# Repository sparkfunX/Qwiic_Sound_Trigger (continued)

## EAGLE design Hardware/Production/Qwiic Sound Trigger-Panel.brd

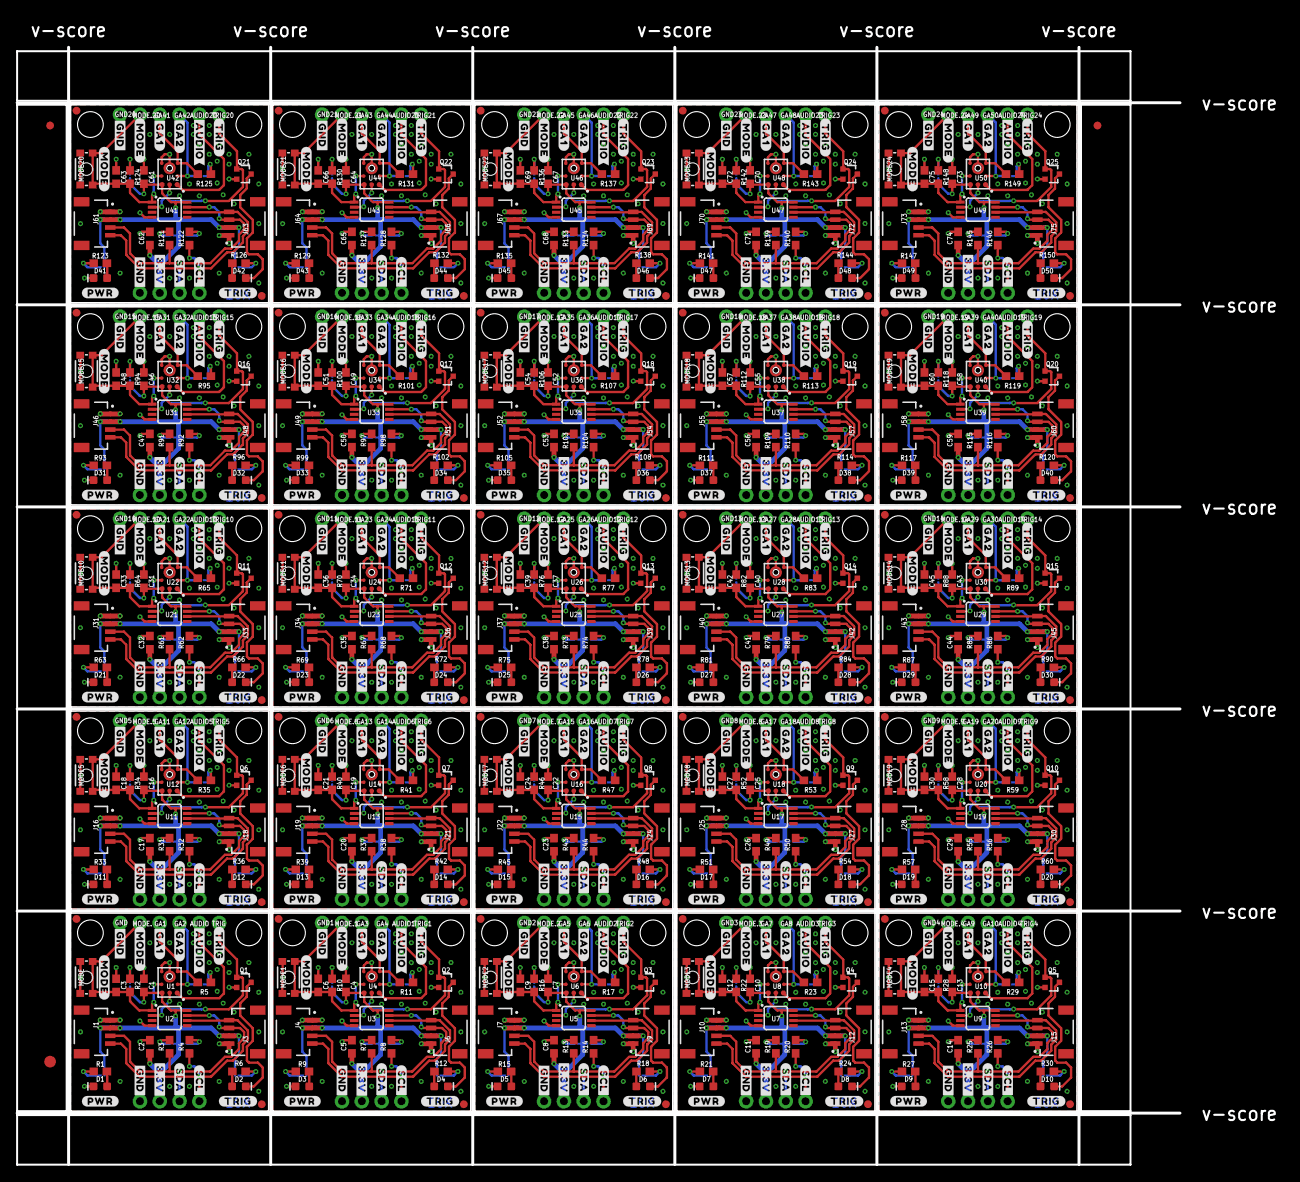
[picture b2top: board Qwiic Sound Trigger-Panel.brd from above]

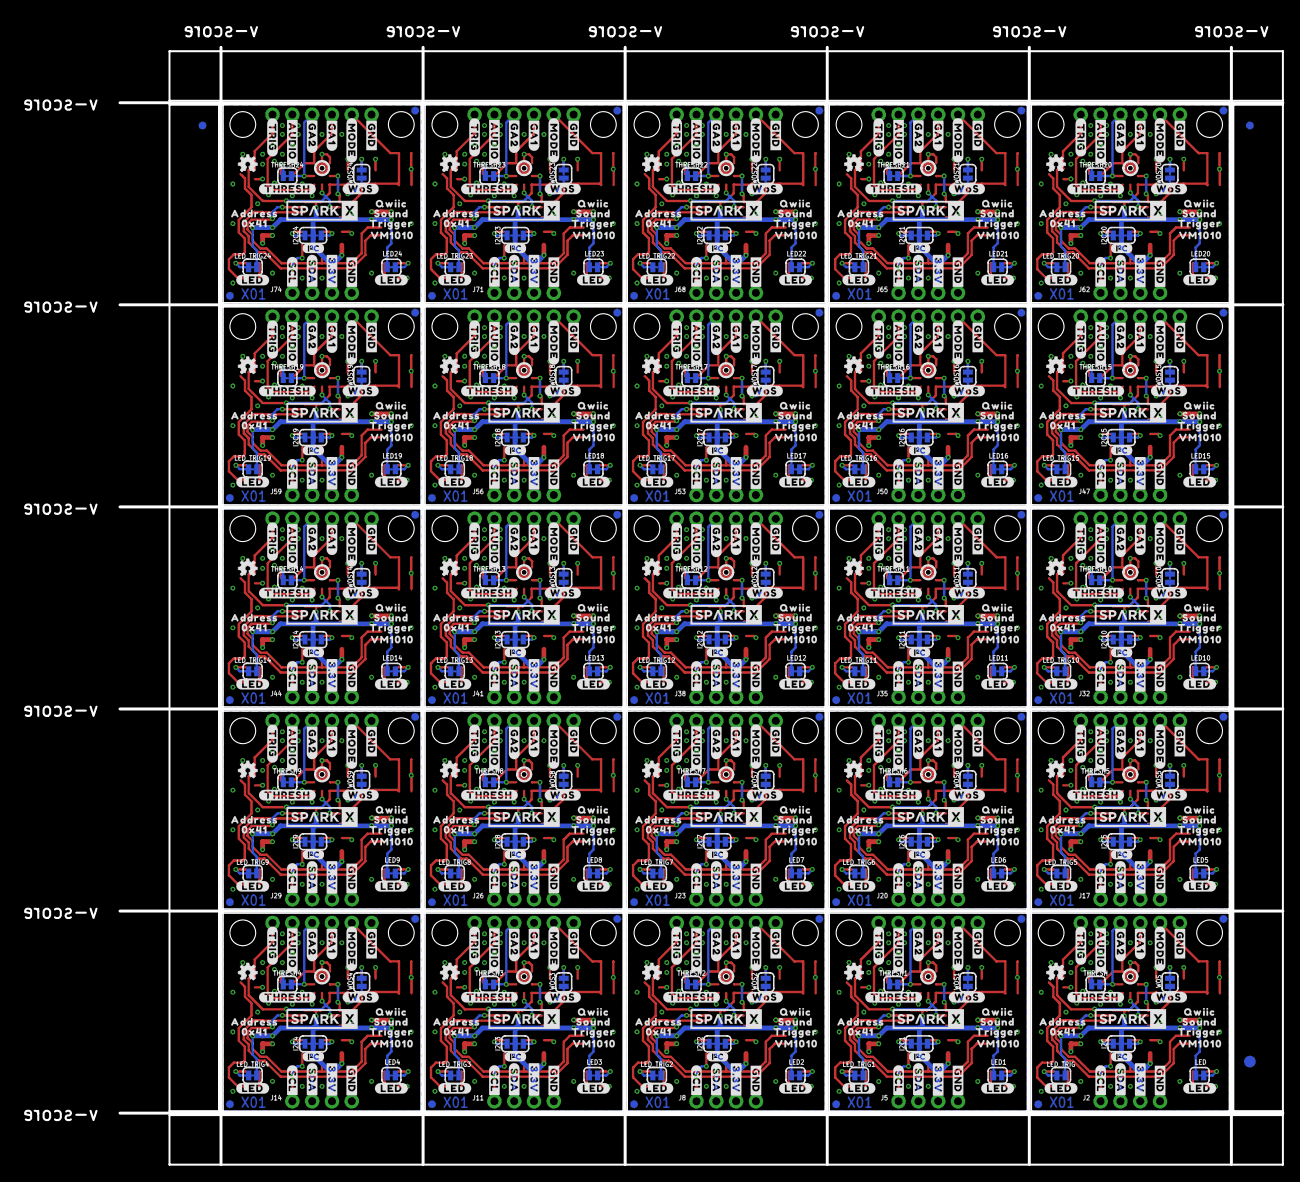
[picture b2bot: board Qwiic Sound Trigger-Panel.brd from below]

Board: 2 copper layers, 149.1 x 143.3 mm, 1831 parts (778 on the bottom side), 450 nets.

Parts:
AUDIO, AUDIO1, AUDIO2, AUDIO3, AUDIO4, AUDIO5, AUDIO6, AUDIO7, AUDIO8, AUDIO9, AUDIO10, AUDIO11, AUDIO12, AUDIO13, AUDIO14, AUDIO15, AUDIO16, AUDIO17, AUDIO18, AUDIO19, AUDIO20, AUDIO21, AUDIO22, AUDIO23, AUDIO24: 1X01_NO_SILK
C1, C3, C4, C6, C7, C9, C10, C12, C13, C15, C16, C18, C19, C21, C22, C24, C25, C27, C28, C30, C31, C33, C34, C36, C37, C39, C40, C42, C43, C45, C46, C48, C49, C51, C52, C54, C55, C57, C58, C60, C61, C63, C64, C66, C67, C69, C70, C72, C73, C75: 0.1uF; 0603
C2, C5, C8, C11, C14, C17, C20, C23, C26, C29, C32, C35, C38, C41, C44, C47, C50, C53, C56, C59, C62, C65, C68, C71, C74: 1.0uF; 0603
D1, D2, D3, D4, D5, D6, D7, D8, D9, D10, D11, D12, D13, D14, D15, D16, D17, D18, D19, D20, D21, D22, D23, D24, D25, D26, D27, D28, D29, D30, D31, D32, D33, D34, D35, D36, D37, D38, D39, D40, D41, D42, D43, D44, D45, D46, D47, D48, D49, D50: RED; LED-0603
E$1, E$2, E$3, E$4: FIDUCIAL-1X2
E$5, E$6: FIDUCIAL-1.5X3
GA1, GA2, GA3, GA4, GA5, GA6, GA7, GA8, GA9, GA10, GA11, GA12, GA13, GA14, GA15, GA16, GA17, GA18, GA19, GA20, GA21, GA22, GA23, GA24, GA25, GA26, GA27, GA28, GA29, GA30, GA31, GA32, GA33, GA34, GA35, GA36, GA37, GA38, GA39, GA40, GA41, GA42, GA43, GA44, GA45, GA46, GA47, GA48, GA49, GA50: 1X01_NO_SILK
GND, GND1, GND2, GND3, GND4, GND5, GND6, GND7, GND8, GND9, GND10, GND11, GND12, GND13, GND14, GND15, GND16, GND17, GND18, GND19, GND20, GND21, GND22, GND23, GND24: 1X01_NO_SILK
I2C, I2C1, I2C2, I2C3, I2C4, I2C5, I2C6, I2C7, I2C8, I2C9, I2C10, I2C11, I2C12, I2C13, I2C14, I2C15, I2C16, I2C17, I2C18, I2C19, I2C20, I2C21, I2C22, I2C23, I2C24: JUMPER-SMT_3_2-NC_TRACE_SILK; SMT-JUMPER_3_2-NC_TRACE_SILK
J1, J3, J4, J6, J7, J9, J10, J12, J13, J15, J16, J18, J19, J21, J22, J24, J25, J27, J28, J30, J31, J33, J34, J36, J37, J39, J40, J42, J43, J45, J46, J48, J49, J51, J52, J54, J55, J57, J58, J60, J61, J63, J64, J66, J67, J69, J70, J72, J73, J75: Qwiic Right Angle; JST04_1MM_RA
J2, J5, J8, J11, J14, J17, J20, J23, J26, J29, J32, J35, J38, J41, J44, J47, J50, J53, J56, J59, J62, J65, J68, J71, J74: PTH; 1X04_NO_SILK
JP1, JP2, JP5, JP6, JP9, JP10, JP11, JP12, JP15, JP16, JP17, JP18, JP21, JP22, JP23, JP24, JP27, JP28, JP29, JP30, JP33, JP34, JP35, JP36, JP39, JP40, JP41, JP42, JP45, JP46, JP47, JP48, JP51, JP52, JP53, JP54, JP57, JP58, JP59, JP60, JP63, JP64, JP65, JP66, JP69, JP70, JP71, JP72, JP75, JP76, JP77, JP78, JP81, JP82, JP83, JP84, JP87, JP88, JP89, JP90, JP93, JP94, JP95, JP96, JP99, JP100, JP101, JP102, JP105, JP106, JP107, JP108, JP111, JP112, JP113, JP114, JP117, JP118, JP119, JP120, JP123, JP124, JP125, JP126, JP129, JP130, JP131, JP132, JP135, JP136, JP137, JP138, JP141, JP142, JP143, JP144, JP147, JP148, JP149, JP150: FIDUCIAL1X2; FIDUCIAL-1X2
JP3, JP4, JP7, JP8, JP13, JP14, JP19, JP20, JP25, JP26, JP31, JP32, JP37, JP38, JP43, JP44, JP49, JP50, JP55, JP56, JP61, JP62, JP67, JP68, JP73, JP74, JP79, JP80, JP85, JP86, JP91, JP92, JP97, JP98, JP103, JP104, JP109, JP110, JP115, JP116, JP121, JP122, JP127, JP128, JP133, JP134, JP139, JP140, JP145, JP146: STAND-OFF
LED, LED1, LED2, LED3, LED4, LED5, LED6, LED7, LED8, LED9, LED10, LED11, LED12, LED13, LED14, LED15, LED16, LED17, LED18, LED19, LED20, LED21, LED22, LED23, LED24: SMT-JUMPER_2_NC_TRACE_SILK
LED_TRIG, LED_TRIG1, LED_TRIG2, LED_TRIG3, LED_TRIG4, LED_TRIG5, LED_TRIG6, LED_TRIG7, LED_TRIG8, LED_TRIG9, LED_TRIG10, LED_TRIG11, LED_TRIG12, LED_TRIG13, LED_TRIG14, LED_TRIG15, LED_TRIG16, LED_TRIG17, LED_TRIG18, LED_TRIG19, LED_TRIG20, LED_TRIG21, LED_TRIG22, LED_TRIG23, LED_TRIG24: SMT-JUMPER_2_NC_TRACE_SILK
LOGO1, LOGO4, LOGO7, LOGO10, LOGO13, LOGO16, LOGO19, LOGO22, LOGO25, LOGO28, LOGO31, LOGO34, LOGO37, LOGO40, LOGO43, LOGO46, LOGO49, LOGO52, LOGO55, LOGO58, LOGO61, LOGO64, LOGO67, LOGO70, LOGO73: OSHW-LOGOMINI; OSHW-LOGO-MINI
LOGO2, LOGO5, LOGO8, LOGO11, LOGO14, LOGO17, LOGO20, LOGO23, LOGO26, LOGO29, LOGO32, LOGO35, LOGO38, LOGO41, LOGO44, LOGO47, LOGO50, LOGO53, LOGO56, LOGO59, LOGO62, LOGO65, LOGO68, LOGO71, LOGO74: SPECIAL_INSTRUCTIONS-ORDERING; ORDERING_INSTRUCTIONS
LOGO3, LOGO6, LOGO9, LOGO12, LOGO15, LOGO18, LOGO21, LOGO24, LOGO27, LOGO30, LOGO33, LOGO36, LOGO39, LOGO42, LOGO45, LOGO48, LOGO51, LOGO54, LOGO57, LOGO60, LOGO63, LOGO66, LOGO69, LOGO72, LOGO75: SPECIAL_INSTRUCTIONS-PRODUCTION; PRODUCTION_INSTRUCTIONS
MODE, MODE1, MODE2, MODE3, MODE4, MODE5, MODE6, MODE7, MODE8, MODE9, MODE10, MODE11, MODE12, MODE13, MODE14, MODE15, MODE16, MODE17, MODE18, MODE19, MODE20, MODE21, MODE22, MODE23, MODE24: MOMENTARY-SWITCH-SPST-SMD-4.6X2.8MM; TACTILE_SWITCH_SMD_4.6X2.8MM
MODE., MODE.1, MODE.2, MODE.3, MODE.4, MODE.5, MODE.6, MODE.7, MODE.8, MODE.9, MODE.10, MODE.11, MODE.12, MODE.13, MODE.14, MODE.15, MODE.16, MODE.17, MODE.18, MODE.19, MODE.20, MODE.21, MODE.22, MODE.23, MODE.24: 1X01_NO_SILK
Q1, Q2, Q3, Q4, Q5, Q6, Q7, Q8, Q9, Q10, Q11, Q12, Q13, Q14, Q15, Q16, Q17, Q18, Q19, Q20, Q21, Q22, Q23, Q24, Q25: 310mA/60V/1.6Ω; SOT323
R1, R6, R9, R12, R15, R18, R21, R24, R27, R30, R33, R36, R39, R42, R45, R48, R51, R54, R57, R60, R63, R66, R69, R72, R75, R78, R81, R84, R87, R90, R93, R96, R99, R102, R105, R108, R111, R114, R117, R120, R123, R126, R129, R132, R135, R138, R141, R144, R147, R150: 1k; 0603
R2, R3, R4, R7, R8, R10, R13, R14, R16, R19, R20, R22, R25, R26, R28, R31, R32, R34, R37, R38, R40, R43, R44, R46, R49, R50, R52, R55, R56, R58, R61, R62, R64, R67, R68, R70, R73, R74, R76, R79, R80, R82, R85, R86, R88, R91, R92, R94, R97, R98, R100, R103, R104, R106, R109, R110, R112, R115, R116, R118, R121, R122, R124, R127, R128, R130, R133, R134, R136, R139, R140, R142, R145, R146, R148: 2.2k; 0603
R5, R11, R17, R23, R29, R35, R41, R47, R53, R59, R65, R71, R77, R83, R89, R95, R101, R107, R113, R119, R125, R131, R137, R143, R149: 20k; 0603
THRESH, THRESH1, THRESH2, THRESH3, THRESH4, THRESH5, THRESH6, THRESH7, THRESH8, THRESH9, THRESH10, THRESH11, THRESH12, THRESH13, THRESH14, THRESH15, THRESH16, THRESH17, THRESH18, THRESH19, THRESH20, THRESH21, THRESH22, THRESH23, THRESH24: SMT-JUMPER_2_NC_TRACE_SILK
TRIG, TRIG1, TRIG2, TRIG3, TRIG4, TRIG5, TRIG6, TRIG7, TRIG8, TRIG9, TRIG10, TRIG11, TRIG12, TRIG13, TRIG14, TRIG15, TRIG16, TRIG17, TRIG18, TRIG19, TRIG20, TRIG21, TRIG22, TRIG23, TRIG24: 1X01_NO_SILK
U1, U4, U6, U8, U10, U12, U14, U16, U18, U20, U22, U24, U26, U28, U30, U32, U34, U36, U38, U40, U42, U44, U46, U48, U50: VM1010
U2, U3, U5, U7, U9, U11, U13, U15, U17, U19, U21, U23, U25, U27, U29, U31, U33, U35, U37, U39, U41, U43, U45, U47, U49: PCA9536; MSOP8
U$1, U$3, U$28, U$37, U$73, U$74, U$108, U$109, U$143, U$144, U$178, U$179, U$213, U$214, U$248, U$249, U$283, U$284, U$318, U$319, U$353, U$354, U$388, U$389, U$423, U$424, U$458, U$459, U$493, U$494, U$528, U$529, U$563, U$564, U$598, U$599, U$633, U$634, U$668, U$669, U$703, U$704, U$738, U$739, U$773, U$774, U$808, U$809, U$843, U$844: #GA1#0
U$2, U$26, U$71, U$106, U$141, U$176, U$211, U$246, U$281, U$316, U$351, U$386, U$421, U$456, U$491, U$526, U$561, U$596, U$631, U$666, U$701, U$736, U$771, U$806, U$841: SPARKX-LOGO4; SPARKX-MEDIUM
U$4, U$5, U$40, U$41, U$75, U$76, U$110, U$111, U$145, U$146, U$180, U$181, U$215, U$216, U$250, U$251, U$285, U$286, U$320, U$321, U$355, U$356, U$390, U$391, U$425, U$426, U$460, U$461, U$495, U$496, U$530, U$531, U$565, U$566, U$600, U$601, U$635, U$636, U$670, U$671, U$705, U$706, U$740, U$741, U$775, U$776, U$810, U$811, U$845, U$846: #GA2#0
U$6, U$7, U$42, U$43, U$77, U$78, U$112, U$113, U$147, U$148, U$182, U$183, U$217, U$218, U$252, U$253, U$287, U$288, U$322, U$323, U$357, U$358, U$392, U$393, U$427, U$428, U$462, U$463, U$497, U$498, U$532, U$533, U$567, U$568, U$602, U$603, U$637, U$638, U$672, U$673, U$707, U$708, U$742, U$743, U$777, U$778, U$812, U$813, U$847, U$848: #AUDIO#0
U$8, U$9, U$25, U$44, U$45, U$70, U$79, U$80, U$105, U$114, U$115, U$140, U$149, U$150, U$175, U$184, U$185, U$210, U$219, U$220, U$245, U$254, U$255, U$280, U$289, U$290, U$315, U$324, U$325, U$350, U$359, U$360, U$385, U$394, U$395, U$420, U$429, U$430, U$455, U$464, U$465, U$490, U$499, U$500, U$525, U$534, U$535, U$560, U$569, U$570, U$595, U$604, U$605, U$630, U$639, U$640, U$665, U$674, U$675, U$700, U$709, U$710, U$735, U$744, U$745, U$770, U$779, U$780, U$805, U$814, U$815, U$840, U$849, U$850, U$875: #MODE#0
U$10, U$27, U$72, U$107, U$142, U$177, U$212, U$247, U$282, U$317, U$352, U$387, U$422, U$457, U$492, U$527, U$562, U$597, U$632, U$667, U$702, U$737, U$772, U$807, U$842: I_SUPER2_C-()-03
U$11, U$12, U$35, U$46, U$47, U$66, U$81, U$82, U$101, U$116, U$117, U$136, U$151, U$152, U$171, U$186, U$187, U$206, U$221, U$222, U$241, U$256, U$257, U$276, U$291, U$292, U$311, U$326, U$327, U$346, U$361, U$362, U$381, U$396, U$397, U$416, U$431, U$432, U$451, U$466, U$467, U$486, U$501, U$502, U$521, U$536, U$537, U$556, U$571, U$572, U$591, U$606, U$607, U$626, U$641, U$642, U$661, U$676, U$677, U$696, U$711, U$712, U$731, U$746, U$747, U$766, U$781, U$782, U$801, U$816, U$817, U$836, U$851, U$852, U$871: #TRIG#0
U$13, U$48, U$83, U$118, U$153, U$188, U$223, U$258, U$293, U$328, U$363, U$398, U$433, U$468, U$503, U$538, U$573, U$608, U$643, U$678, U$713, U$748, U$783, U$818, U$853: #PWR#0
U$14, U$36, U$49, U$67, U$84, U$102, U$119, U$137, U$154, U$172, U$189, U$207, U$224, U$242, U$259, U$277, U$294, U$312, U$329, U$347, U$364, U$382, U$399, U$417, U$434, U$452, U$469, U$487, U$504, U$522, U$539, U$557, U$574, U$592, U$609, U$627, U$644, U$662, U$679, U$697, U$714, U$732, U$749, U$767, U$784, U$802, U$819, U$837, U$854, U$872: #LED#0
U$15, U$50, U$85, U$120, U$155, U$190, U$225, U$260, U$295, U$330, U$365, U$400, U$435, U$470, U$505, U$540, U$575, U$610, U$645, U$680, U$715, U$750, U$785, U$820, U$855: #THRESH#0
U$16, U$51, U$86, U$121, U$156, U$191, U$226, U$261, U$296, U$331, U$366, U$401, U$436, U$471, U$506, U$541, U$576, U$611, U$646, U$681, U$716, U$751, U$786, U$821, U$856: #WOS#0
U$17, U$18, U$38, U$39, U$52, U$53, U$68, U$69, U$87, U$88, U$103, U$104, U$122, U$123, U$138, U$139, U$157, U$158, U$173, U$174, U$192, U$193, U$208, U$209, U$227, U$228, U$243, U$244, U$262, U$263, U$278, U$279, U$297, U$298, U$313, U$314, U$332, U$333, U$348, U$349, U$367, U$368, U$383, U$384, U$402, U$403, U$418, U$419, U$437, U$438, U$453, U$454, U$472, U$473, U$488, U$489, U$507, U$508, U$523, U$524, U$542, U$543, U$558, U$559, U$577, U$578, U$593, U$594, U$612, U$613, U$628, U$629, U$647, U$648, U$663, U$664, U$682, U$683, U$698, U$699, U$717, U$718, U$733, U$734, U$752, U$753, U$768, U$769, U$787, U$788, U$803, U$804, U$822, U$823, U$838, U$839, U$857, U$858, U$873, U$874: #GND#0
U$19, U$20, U$54, U$55, U$89, U$90, U$124, U$125, U$159, U$160, U$194, U$195, U$229, U$230, U$264, U$265, U$299, U$300, U$334, U$335, U$369, U$370, U$404, U$405, U$439, U$440, U$474, U$475, U$509, U$510, U$544, U$545, U$579, U$580, U$614, U$615, U$649, U$650, U$684, U$685, U$719, U$720, U$754, U$755, U$789, U$790, U$824, U$825, U$859, U$860: #3#3V#0
U$21, U$22, U$56, U$57, U$91, U$92, U$126, U$127, U$161, U$162, U$196, U$197, U$231, U$232, U$266, U$267, U$301, U$302, U$336, U$337, U$371, U$372, U$406, U$407, U$441, U$442, U$476, U$477, U$511, U$512, U$546, U$547, U$581, U$582, U$616, U$617, U$651, U$652, U$686, U$687, U$721, U$722, U$756, U$757, U$791, U$792, U$826, U$827, U$861, U$862: #SDA#0
U$23, U$24, U$58, U$59, U$93, U$94, U$128, U$129, U$163, U$164, U$198, U$199, U$233, U$234, U$268, U$269, U$303, U$304, U$338, U$339, U$373, U$374, U$408, U$409, U$443, U$444, U$478, U$479, U$513, U$514, U$548, U$549, U$583, U$584, U$618, U$619, U$653, U$654, U$688, U$689, U$723, U$724, U$758, U$759, U$793, U$794, U$828, U$829, U$863, U$864: #SCL#0
U$29, U$60, U$95, U$130, U$165, U$200, U$235, U$270, U$305, U$340, U$375, U$410, U$445, U$480, U$515, U$550, U$585, U$620, U$655, U$690, U$725, U$760, U$795, U$830, U$865: QWIIC0
U$30, U$61, U$96, U$131, U$166, U$201, U$236, U$271, U$306, U$341, U$376, U$411, U$446, U$481, U$516, U$551, U$586, U$621, U$656, U$691, U$726, U$761, U$796, U$831, U$866: SOUND0
U$31, U$62, U$97, U$132, U$167, U$202, U$237, U$272, U$307, U$342, U$377, U$412, U$447, U$482, U$517, U$552, U$587, U$622, U$657, U$692, U$727, U$762, U$797, U$832, U$867: TRIGGER0
U$32, U$63, U$98, U$133, U$168, U$203, U$238, U$273, U$308, U$343, U$378, U$413, U$448, U$483, U$518, U$553, U$588, U$623, U$658, U$693, U$728, U$763, U$798, U$833, U$868: VM10100
U$33, U$64, U$99, U$134, U$169, U$204, U$239, U$274, U$309, U$344, U$379, U$414, U$449, U$484, U$519, U$554, U$589, U$624, U$659, U$694, U$729, U$764, U$799, U$834, U$869: ADDRESS0
U$34, U$65, U$100, U$135, U$170, U$205, U$240, U$275, U$310, U$345, U$380, U$415, U$450, U$485, U$520, U$555, U$590, U$625, U$660, U$695, U$730, U$765, U$800, U$835, U$870: 0X410
WOS, WOS1, WOS2, WOS3, WOS4, WOS5, WOS6, WOS7, WOS8, WOS9, WOS10, WOS11, WOS12, WOS13, WOS14, WOS15, WOS16, WOS17, WOS18, WOS19, WOS20, WOS21, WOS22, WOS23, WOS24: SMT-JUMPER_2_NC_TRACE_SILK

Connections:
3.3V: C1.1, C2.1, I2C.2, J1.2, J2.2, J3.2, LED.2, LED_TRIG.2, U1.6, U2.8, WOS.2
3.3V1: C4.1, C5.1, I2C1.2, J4.2, J5.2, J6.2, LED1.2, LED_TRIG1.2, U3.8, U4.6, WOS1.2
3.3V2: C7.1, C8.1, I2C2.2, J7.2, J8.2, J9.2, LED2.2, LED_TRIG2.2, U5.8, U6.6, WOS2.2
3.3V3: C10.1, C11.1, I2C3.2, J10.2, J11.2, J12.2, LED3.2, LED_TRIG3.2, U7.8, U8.6, WOS3.2
3.3V4: C13.1, C14.1, I2C4.2, J13.2, J14.2, J15.2, LED4.2, LED_TRIG4.2, U9.8, U10.6, WOS4.2
3.3V5: C16.1, C17.1, I2C5.2, J16.2, J17.2, J18.2, LED5.2, LED_TRIG5.2, U11.8, U12.6, WOS5.2
3.3V6: C19.1, C20.1, I2C6.2, J19.2, J20.2, J21.2, LED6.2, LED_TRIG6.2, U13.8, U14.6, WOS6.2
3.3V7: C22.1, C23.1, I2C7.2, J22.2, J23.2, J24.2, LED7.2, LED_TRIG7.2, U15.8, U16.6, WOS7.2
3.3V8: C25.1, C26.1, I2C8.2, J25.2, J26.2, J27.2, LED8.2, LED_TRIG8.2, U17.8, U18.6, WOS8.2
3.3V9: C28.1, C29.1, I2C9.2, J28.2, J29.2, J30.2, LED9.2, LED_TRIG9.2, U19.8, U20.6, WOS9.2
3.3V10: C31.1, C32.1, I2C10.2, J31.2, J32.2, J33.2, LED10.2, LED_TRIG10.2, U21.8, U22.6, WOS10.2
3.3V11: C34.1, C35.1, I2C11.2, J34.2, J35.2, J36.2, LED11.2, LED_TRIG11.2, U23.8, U24.6, WOS11.2
3.3V12: C37.1, C38.1, I2C12.2, J37.2, J38.2, J39.2, LED12.2, LED_TRIG12.2, U25.8, U26.6, WOS12.2
3.3V13: C40.1, C41.1, I2C13.2, J40.2, J41.2, J42.2, LED13.2, LED_TRIG13.2, U27.8, U28.6, WOS13.2
3.3V14: C43.1, C44.1, I2C14.2, J43.2, J44.2, J45.2, LED14.2, LED_TRIG14.2, U29.8, U30.6, WOS14.2
3.3V15: C46.1, C47.1, I2C15.2, J46.2, J47.2, J48.2, LED15.2, LED_TRIG15.2, U31.8, U32.6, WOS15.2
3.3V16: C49.1, C50.1, I2C16.2, J49.2, J50.2, J51.2, LED16.2, LED_TRIG16.2, U33.8, U34.6, WOS16.2
3.3V17: C52.1, C53.1, I2C17.2, J52.2, J53.2, J54.2, LED17.2, LED_TRIG17.2, U35.8, U36.6, WOS17.2
3.3V18: C55.1, C56.1, I2C18.2, J55.2, J56.2, J57.2, LED18.2, LED_TRIG18.2, U37.8, U38.6, WOS18.2
3.3V19: C58.1, C59.1, I2C19.2, J58.2, J59.2, J60.2, LED19.2, LED_TRIG19.2, U39.8, U40.6, WOS19.2
3.3V20: C61.1, C62.1, I2C20.2, J61.2, J62.2, J63.2, LED20.2, LED_TRIG20.2, U41.8, U42.6, WOS20.2
3.3V21: C64.1, C65.1, I2C21.2, J64.2, J65.2, J66.2, LED21.2, LED_TRIG21.2, U43.8, U44.6, WOS21.2
3.3V22: C67.1, C68.1, I2C22.2, J67.2, J68.2, J69.2, LED22.2, LED_TRIG22.2, U45.8, U46.6, WOS22.2
3.3V23: C70.1, C71.1, I2C23.2, J70.2, J71.2, J72.2, LED23.2, LED_TRIG23.2, U47.8, U48.6, WOS23.2
3.3V24: C73.1, C74.1, I2C24.2, J73.2, J74.2, J75.2, LED24.2, LED_TRIG24.2, U49.8, U50.6, WOS24.2
AUDIO: AUDIO.1, U1.1
AUDIO1: AUDIO1.1, U4.1
AUDIO2: AUDIO2.1, U6.1
AUDIO3: AUDIO3.1, U8.1
AUDIO4: AUDIO4.1, U10.1
AUDIO5: AUDIO5.1, U12.1
AUDIO6: AUDIO6.1, U14.1
AUDIO7: AUDIO7.1, U16.1
AUDIO8: AUDIO8.1, U18.1
AUDIO9: AUDIO9.1, U20.1
AUDIO10: AUDIO10.1, U22.1
AUDIO11: AUDIO11.1, U24.1
AUDIO12: AUDIO12.1, U26.1
AUDIO13: AUDIO13.1, U28.1
AUDIO14: AUDIO14.1, U30.1
AUDIO15: AUDIO15.1, U32.1
AUDIO16: AUDIO16.1, U34.1
AUDIO17: AUDIO17.1, U36.1
AUDIO18: AUDIO18.1, U38.1
AUDIO19: AUDIO19.1, U40.1
AUDIO20: AUDIO20.1, U42.1
AUDIO21: AUDIO21.1, U44.1
AUDIO22: AUDIO22.1, U46.1
AUDIO23: AUDIO23.1, U48.1
AUDIO24: AUDIO24.1, U50.1
GA1: GA1.1, R5.1, U1.3
GA2: GA2.1, THRESH.2, U1.2
GA3: GA4.1, THRESH1.2, U4.2
GA4: GA3.1, R11.1, U4.3
GA5: GA6.1, THRESH2.2, U6.2
GA6: GA5.1, R17.1, U6.3
GA7: GA8.1, THRESH3.2, U8.2
GA8: GA7.1, R23.1, U8.3
GA9: GA10.1, THRESH4.2, U10.2
GA10: GA9.1, R29.1, U10.3
GA11: GA12.1, THRESH5.2, U12.2
GA12: GA11.1, R35.1, U12.3
GA13: GA14.1, THRESH6.2, U14.2
GA14: GA13.1, R41.1, U14.3
GA15: GA16.1, THRESH7.2, U16.2
GA16: GA15.1, R47.1, U16.3
GA17: GA18.1, THRESH8.2, U18.2
GA18: GA17.1, R53.1, U18.3
GA19: GA20.1, THRESH9.2, U20.2
GA20: GA19.1, R59.1, U20.3
GA21: GA22.1, THRESH10.2, U22.2
GA22: GA21.1, R65.1, U22.3
GA23: GA24.1, THRESH11.2, U24.2
GA24: GA23.1, R71.1, U24.3
GA25: GA26.1, THRESH12.2, U26.2
GA26: GA25.1, R77.1, U26.3
GA27: GA28.1, THRESH13.2, U28.2
GA28: GA27.1, R83.1, U28.3
GA29: GA30.1, THRESH14.2, U30.2
GA30: GA29.1, R89.1, U30.3
GA31: GA32.1, THRESH15.2, U32.2
GA32: GA31.1, R95.1, U32.3
GA33: GA34.1, THRESH16.2, U34.2
GA34: GA33.1, R101.1, U34.3
GA35: GA36.1, THRESH17.2, U36.2
GA36: GA35.1, R107.1, U36.3
GA37: GA38.1, THRESH18.2, U38.2
GA38: GA37.1, R113.1, U38.3
GA39: GA40.1, THRESH19.2, U40.2
GA40: GA39.1, R119.1, U40.3
GA41: GA42.1, THRESH20.2, U42.2
GA42: GA41.1, R125.1, U42.3
GA43: GA44.1, THRESH21.2, U44.2
GA44: GA43.1, R131.1, U44.3
GA45: GA46.1, THRESH22.2, U46.2
GA46: GA45.1, R137.1, U46.3
GA47: GA48.1, THRESH23.2, U48.2
GA48: GA47.1, R143.1, U48.3
GA49: GA50.1, THRESH24.2, U50.2
GA50: GA49.1, R149.1, U50.3
GND: C1.2, C2.2, C3.2, D1.C, GND.1, J1.1, J2.1, J3.1, MODE.1, MODE.2, Q1.2, U1.4, U1.8, U2.4
GND1: C4.2, C5.2, C6.2, D3.C, GND1.1, J4.1, J5.1, J6.1, MODE1.1, MODE1.2, Q2.2, U3.4, U4.4, U4.8
GND2: C7.2, C8.2, C9.2, D5.C, GND2.1, J7.1, J8.1, J9.1, MODE2.1, MODE2.2, Q3.2, U5.4, U6.4, U6.8
GND3: C10.2, C11.2, C12.2, D7.C, GND3.1, J10.1, J11.1, J12.1, MODE3.1, MODE3.2, Q4.2, U7.4, U8.4, U8.8
GND4: C13.2, C14.2, C15.2, D9.C, GND4.1, J13.1, J14.1, J15.1, MODE4.1, MODE4.2, Q5.2, U9.4, U10.4, U10.8
GND5: C16.2, C17.2, C18.2, D11.C, GND5.1, J16.1, J17.1, J18.1, MODE5.1, MODE5.2, Q6.2, U11.4, U12.4, U12.8
GND6: C19.2, C20.2, C21.2, D13.C, GND6.1, J19.1, J20.1, J21.1, MODE6.1, MODE6.2, Q7.2, U13.4, U14.4, U14.8
GND7: C22.2, C23.2, C24.2, D15.C, GND7.1, J22.1, J23.1, J24.1, MODE7.1, MODE7.2, Q8.2, U15.4, U16.4, U16.8
GND8: C25.2, C26.2, C27.2, D17.C, GND8.1, J25.1, J26.1, J27.1, MODE8.1, MODE8.2, Q9.2, U17.4, U18.4, U18.8
GND9: C28.2, C29.2, C30.2, D19.C, GND9.1, J28.1, J29.1, J30.1, MODE9.1, MODE9.2, Q10.2, U19.4, U20.4, U20.8
GND10: C31.2, C32.2, C33.2, D21.C, GND10.1, J31.1, J32.1, J33.1, MODE10.1, MODE10.2, Q11.2, U21.4, U22.4, U22.8
GND11: C34.2, C35.2, C36.2, D23.C, GND11.1, J34.1, J35.1, J36.1, MODE11.1, MODE11.2, Q12.2, U23.4, U24.4, U24.8
GND12: C37.2, C38.2, C39.2, D25.C, GND12.1, J37.1, J38.1, J39.1, MODE12.1, MODE12.2, Q13.2, U25.4, U26.4, U26.8
GND13: C40.2, C41.2, C42.2, D27.C, GND13.1, J40.1, J41.1, J42.1, MODE13.1, MODE13.2, Q14.2, U27.4, U28.4, U28.8
GND14: C43.2, C44.2, C45.2, D29.C, GND14.1, J43.1, J44.1, J45.1, MODE14.1, MODE14.2, Q15.2, U29.4, U30.4, U30.8
GND15: C46.2, C47.2, C48.2, D31.C, GND15.1, J46.1, J47.1, J48.1, MODE15.1, MODE15.2, Q16.2, U31.4, U32.4, U32.8
GND16: C49.2, C50.2, C51.2, D33.C, GND16.1, J49.1, J50.1, J51.1, MODE16.1, MODE16.2, Q17.2, U33.4, U34.4, U34.8
GND17: C52.2, C53.2, C54.2, D35.C, GND17.1, J52.1, J53.1, J54.1, MODE17.1, MODE17.2, Q18.2, U35.4, U36.4, U36.8
GND18: C55.2, C56.2, C57.2, D37.C, GND18.1, J55.1, J56.1, J57.1, MODE18.1, MODE18.2, Q19.2, U37.4, U38.4, U38.8
GND19: C58.2, C59.2, C60.2, D39.C, GND19.1, J58.1, J59.1, J60.1, MODE19.1, MODE19.2, Q20.2, U39.4, U40.4, U40.8
GND20: C61.2, C62.2, C63.2, D41.C, GND20.1, J61.1, J62.1, J63.1, MODE20.1, MODE20.2, Q21.2, U41.4, U42.4, U42.8
GND21: C64.2, C65.2, C66.2, D43.C, GND21.1, J64.1, J65.1, J66.1, MODE21.1, MODE21.2, Q22.2, U43.4, U44.4, U44.8
GND22: C67.2, C68.2, C69.2, D45.C, GND22.1, J67.1, J68.1, J69.1, MODE22.1, MODE22.2, Q23.2, U45.4, U46.4, U46.8
GND23: C70.2, C71.2, C72.2, D47.C, GND23.1, J70.1, J71.1, J72.1, MODE23.1, MODE23.2, Q24.2, U47.4, U48.4, U48.8
GND24: C73.2, C74.2, C75.2, D49.C, GND24.1, J73.1, J74.1, J75.1, MODE24.1, MODE24.2, Q25.2, U49.4, U50.4, U50.8
MODE: C3.1, MODE.3, MODE.4, MODE..1, R2.1, U1.5, U2.1
MODE1: C6.1, MODE1.3, MODE1.4, MODE.1.1, R10.1, U3.1, U4.5
MODE2: C9.1, MODE2.3, MODE2.4, MODE.2.1, R16.1, U5.1, U6.5
MODE3: C12.1, MODE3.3, MODE3.4, MODE.3.1, R22.1, U7.1, U8.5
MODE4: C15.1, MODE4.3, MODE4.4, MODE.4.1, R28.1, U9.1, U10.5
MODE5: C18.1, MODE5.3, MODE5.4, MODE.5.1, R34.1, U11.1, U12.5
MODE6: C21.1, MODE6.3, MODE6.4, MODE.6.1, R40.1, U13.1, U14.5
MODE7: C24.1, MODE7.3, MODE7.4, MODE.7.1, R46.1, U15.1, U16.5
MODE8: C27.1, MODE8.3, MODE8.4, MODE.8.1, R52.1, U17.1, U18.5
MODE9: C30.1, MODE9.3, MODE9.4, MODE.9.1, R58.1, U19.1, U20.5
MODE10: C33.1, MODE10.3, MODE10.4, MODE.10.1, R64.1, U21.1, U22.5
MODE11: C36.1, MODE11.3, MODE11.4, MODE.11.1, R70.1, U23.1, U24.5
MODE12: C39.1, MODE12.3, MODE12.4, MODE.12.1, R76.1, U25.1, U26.5
MODE13: C42.1, MODE13.3, MODE13.4, MODE.13.1, R82.1, U27.1, U28.5
MODE14: C45.1, MODE14.3, MODE14.4, MODE.14.1, R88.1, U29.1, U30.5
MODE15: C48.1, MODE15.3, MODE15.4, MODE.15.1, R94.1, U31.1, U32.5
MODE16: C51.1, MODE16.3, MODE16.4, MODE.16.1, R100.1, U33.1, U34.5
MODE17: C54.1, MODE17.3, MODE17.4, MODE.17.1, R106.1, U35.1, U36.5
MODE18: C57.1, MODE18.3, MODE18.4, MODE.18.1, R112.1, U37.1, U38.5
MODE19: C60.1, MODE19.3, MODE19.4, MODE.19.1, R118.1, U39.1, U40.5
MODE20: C63.1, MODE20.3, MODE20.4, MODE.20.1, R124.1, U41.1, U42.5
MODE21: C66.1, MODE21.3, MODE21.4, MODE.21.1, R130.1, U43.1, U44.5
MODE22: C69.1, MODE22.3, MODE22.4, MODE.22.1, R136.1, U45.1, U46.5
MODE23: C72.1, MODE23.3, MODE23.4, MODE.23.1, R142.1, U47.1, U48.5
MODE24: C75.1, MODE24.3, MODE24.4, MODE.24.1, R148.1, U49.1, U50.5
unnamed: I2C.1, R4.2
unnamed: I2C.3, R3.2
unnamed: D1.A, R1.1
unnamed: LED.1, R1.2
unnamed: R2.2, WOS.1
unnamed: R5.2, THRESH.1
unnamed: D2.A, R6.1
unnamed: LED_TRIG.1, R6.2
unnamed: D2.C, Q1.3
unnamed: I2C1.1, R8.2
unnamed: I2C1.3, R7.2
unnamed: D3.A, R9.1
unnamed: LED1.1, R9.2
unnamed: R10.2, WOS1.1
unnamed: R11.2, THRESH1.1
unnamed: D4.A, R12.1
unnamed: LED_TRIG1.1, R12.2
unnamed: D4.C, Q2.3
unnamed: I2C2.1, R14.2
unnamed: I2C2.3, R13.2
unnamed: D5.A, R15.1
unnamed: LED2.1, R15.2
unnamed: R16.2, WOS2.1
unnamed: R17.2, THRESH2.1
unnamed: D6.A, R18.1
unnamed: LED_TRIG2.1, R18.2
unnamed: D6.C, Q3.3
unnamed: I2C3.1, R20.2
unnamed: I2C3.3, R19.2
unnamed: D7.A, R21.1
unnamed: LED3.1, R21.2
unnamed: R22.2, WOS3.1
unnamed: R23.2, THRESH3.1
unnamed: D8.A, R24.1
unnamed: LED_TRIG3.1, R24.2
unnamed: D8.C, Q4.3
unnamed: I2C4.1, R26.2
unnamed: I2C4.3, R25.2
unnamed: D9.A, R27.1
unnamed: LED4.1, R27.2
unnamed: R28.2, WOS4.1
unnamed: R29.2, THRESH4.1
unnamed: D10.A, R30.1
unnamed: LED_TRIG4.1, R30.2
unnamed: D10.C, Q5.3
unnamed: I2C5.1, R32.2
unnamed: I2C5.3, R31.2
unnamed: D11.A, R33.1
unnamed: LED5.1, R33.2
unnamed: R34.2, WOS5.1
unnamed: R35.2, THRESH5.1
unnamed: D12.A, R36.1
unnamed: LED_TRIG5.1, R36.2
unnamed: D12.C, Q6.3
unnamed: I2C6.1, R38.2
unnamed: I2C6.3, R37.2
unnamed: D13.A, R39.1
unnamed: LED6.1, R39.2
unnamed: R40.2, WOS6.1
unnamed: R41.2, THRESH6.1
unnamed: D14.A, R42.1
unnamed: LED_TRIG6.1, R42.2
unnamed: D14.C, Q7.3
unnamed: I2C7.1, R44.2
unnamed: I2C7.3, R43.2
unnamed: D15.A, R45.1
unnamed: LED7.1, R45.2
unnamed: R46.2, WOS7.1
unnamed: R47.2, THRESH7.1
unnamed: D16.A, R48.1
unnamed: LED_TRIG7.1, R48.2
unnamed: D16.C, Q8.3
unnamed: I2C8.1, R50.2
unnamed: I2C8.3, R49.2
unnamed: D17.A, R51.1
unnamed: LED8.1, R51.2
unnamed: R52.2, WOS8.1
unnamed: R53.2, THRESH8.1
unnamed: D18.A, R54.1
unnamed: LED_TRIG8.1, R54.2
unnamed: D18.C, Q9.3
unnamed: I2C9.1, R56.2
unnamed: I2C9.3, R55.2
unnamed: D19.A, R57.1
unnamed: LED9.1, R57.2
unnamed: R58.2, WOS9.1
unnamed: R59.2, THRESH9.1
unnamed: D20.A, R60.1
unnamed: LED_TRIG9.1, R60.2
unnamed: D20.C, Q10.3
unnamed: I2C10.1, R62.2
unnamed: I2C10.3, R61.2
unnamed: D21.A, R63.1
unnamed: LED10.1, R63.2
unnamed: R64.2, WOS10.1
unnamed: R65.2, THRESH10.1
unnamed: D22.A, R66.1
unnamed: LED_TRIG10.1, R66.2
unnamed: D22.C, Q11.3
unnamed: I2C11.1, R68.2
unnamed: I2C11.3, R67.2
unnamed: D23.A, R69.1
unnamed: LED11.1, R69.2
unnamed: R70.2, WOS11.1
unnamed: R71.2, THRESH11.1
unnamed: D24.A, R72.1
unnamed: LED_TRIG11.1, R72.2
unnamed: D24.C, Q12.3
unnamed: I2C12.1, R74.2
unnamed: I2C12.3, R73.2
unnamed: D25.A, R75.1
unnamed: LED12.1, R75.2
unnamed: R76.2, WOS12.1
unnamed: R77.2, THRESH12.1
unnamed: D26.A, R78.1
unnamed: LED_TRIG12.1, R78.2
unnamed: D26.C, Q13.3
unnamed: I2C13.1, R80.2
unnamed: I2C13.3, R79.2
unnamed: D27.A, R81.1
unnamed: LED13.1, R81.2
unnamed: R82.2, WOS13.1
unnamed: R83.2, THRESH13.1
unnamed: D28.A, R84.1
unnamed: LED_TRIG13.1, R84.2
unnamed: D28.C, Q14.3
unnamed: I2C14.1, R86.2
unnamed: I2C14.3, R85.2
unnamed: D29.A, R87.1
unnamed: LED14.1, R87.2
unnamed: R88.2, WOS14.1
unnamed: R89.2, THRESH14.1
unnamed: D30.A, R90.1
unnamed: LED_TRIG14.1, R90.2
unnamed: D30.C, Q15.3
unnamed: I2C15.1, R92.2
unnamed: I2C15.3, R91.2
unnamed: D31.A, R93.1
unnamed: LED15.1, R93.2
unnamed: R94.2, WOS15.1
unnamed: R95.2, THRESH15.1
unnamed: D32.A, R96.1
unnamed: LED_TRIG15.1, R96.2
unnamed: D32.C, Q16.3
unnamed: I2C16.1, R98.2
unnamed: I2C16.3, R97.2
unnamed: D33.A, R99.1
unnamed: LED16.1, R99.2
unnamed: R100.2, WOS16.1
unnamed: R101.2, THRESH16.1
unnamed: D34.A, R102.1
unnamed: LED_TRIG16.1, R102.2
unnamed: D34.C, Q17.3
unnamed: I2C17.1, R104.2
unnamed: I2C17.3, R103.2
unnamed: D35.A, R105.1
unnamed: LED17.1, R105.2
unnamed: R106.2, WOS17.1
unnamed: R107.2, THRESH17.1
unnamed: D36.A, R108.1
unnamed: LED_TRIG17.1, R108.2
unnamed: D36.C, Q18.3
unnamed: I2C18.1, R110.2
unnamed: I2C18.3, R109.2
unnamed: D37.A, R111.1
unnamed: LED18.1, R111.2
unnamed: R112.2, WOS18.1
unnamed: R113.2, THRESH18.1
unnamed: D38.A, R114.1
unnamed: LED_TRIG18.1, R114.2
unnamed: D38.C, Q19.3
unnamed: I2C19.1, R116.2
unnamed: I2C19.3, R115.2
unnamed: D39.A, R117.1
unnamed: LED19.1, R117.2
unnamed: R118.2, WOS19.1
unnamed: R119.2, THRESH19.1
unnamed: D40.A, R120.1
unnamed: LED_TRIG19.1, R120.2
unnamed: D40.C, Q20.3
unnamed: I2C20.1, R122.2
unnamed: I2C20.3, R121.2
unnamed: D41.A, R123.1
unnamed: LED20.1, R123.2
unnamed: R124.2, WOS20.1
unnamed: R125.2, THRESH20.1
unnamed: D42.A, R126.1
unnamed: LED_TRIG20.1, R126.2
unnamed: D42.C, Q21.3
unnamed: I2C21.1, R128.2
unnamed: I2C21.3, R127.2
unnamed: D43.A, R129.1
unnamed: LED21.1, R129.2
unnamed: R130.2, WOS21.1
unnamed: R131.2, THRESH21.1
unnamed: D44.A, R132.1
unnamed: LED_TRIG21.1, R132.2
unnamed: D44.C, Q22.3
unnamed: I2C22.1, R134.2
unnamed: I2C22.3, R133.2
unnamed: D45.A, R135.1
unnamed: LED22.1, R135.2
unnamed: R136.2, WOS22.1
unnamed: R137.2, THRESH22.1
unnamed: D46.A, R138.1
unnamed: LED_TRIG22.1, R138.2
unnamed: D46.C, Q23.3
unnamed: I2C23.1, R140.2
unnamed: I2C23.3, R139.2
unnamed: D47.A, R141.1
unnamed: LED23.1, R141.2
unnamed: R142.2, WOS23.1
unnamed: R143.2, THRESH23.1
unnamed: D48.A, R144.1
unnamed: LED_TRIG23.1, R144.2
unnamed: D48.C, Q24.3
unnamed: I2C24.1, R146.2
unnamed: I2C24.3, R145.2
unnamed: D49.A, R147.1
unnamed: LED24.1, R147.2
unnamed: R148.2, WOS24.1
unnamed: R149.2, THRESH24.1
unnamed: D50.A, R150.1
unnamed: LED_TRIG24.1, R150.2
unnamed: D50.C, Q25.3
SCL: J1.4, J2.4, J3.4, R4.1, U2.6
SCL1: J4.4, J5.4, J6.4, R8.1, U3.6
SCL2: J7.4, J8.4, J9.4, R14.1, U5.6
SCL3: J10.4, J11.4, J12.4, R20.1, U7.6
SCL4: J13.4, J14.4, J15.4, R26.1, U9.6
SCL5: J16.4, J17.4, J18.4, R32.1, U11.6
SCL6: J19.4, J20.4, J21.4, R38.1, U13.6
SCL7: J22.4, J23.4, J24.4, R44.1, U15.6
SCL8: J25.4, J26.4, J27.4, R50.1, U17.6
SCL9: J28.4, J29.4, J30.4, R56.1, U19.6
SCL10: J31.4, J32.4, J33.4, R62.1, U21.6
SCL11: J34.4, J35.4, J36.4, R68.1, U23.6
SCL12: J37.4, J38.4, J39.4, R74.1, U25.6
SCL13: J40.4, J41.4, J42.4, R80.1, U27.6
SCL14: J43.4, J44.4, J45.4, R86.1, U29.6
SCL15: J46.4, J47.4, J48.4, R92.1, U31.6
SCL16: J49.4, J50.4, J51.4, R98.1, U33.6
SCL17: J52.4, J53.4, J54.4, R104.1, U35.6
SCL18: J55.4, J56.4, J57.4, R110.1, U37.6
SCL19: J58.4, J59.4, J60.4, R116.1, U39.6
SCL20: J61.4, J62.4, J63.4, R122.1, U41.6
SCL21: J64.4, J65.4, J66.4, R128.1, U43.6
SCL22: J67.4, J68.4, J69.4, R134.1, U45.6
SCL23: J70.4, J71.4, J72.4, R140.1, U47.6
SCL24: J73.4, J74.4, J75.4, R146.1, U49.6
SDA: J1.3, J2.3, J3.3, R3.1, U2.7
SDA1: J4.3, J5.3, J6.3, R7.1, U3.7
SDA2: J7.3, J8.3, J9.3, R13.1, U5.7
SDA3: J10.3, J11.3, J12.3, R19.1, U7.7
SDA4: J13.3, J14.3, J15.3, R25.1, U9.7
SDA5: J16.3, J17.3, J18.3, R31.1, U11.7
SDA6: J19.3, J20.3, J21.3, R37.1, U13.7
SDA7: J22.3, J23.3, J24.3, R43.1, U15.7
SDA8: J25.3, J26.3, J27.3, R49.1, U17.7
SDA9: J28.3, J29.3, J30.3, R55.1, U19.7
SDA10: J31.3, J32.3, J33.3, R61.1, U21.7
SDA11: J34.3, J35.3, J36.3, R67.1, U23.7
SDA12: J37.3, J38.3, J39.3, R73.1, U25.7
SDA13: J40.3, J41.3, J42.3, R79.1, U27.7
SDA14: J43.3, J44.3, J45.3, R85.1, U29.7
SDA15: J46.3, J47.3, J48.3, R91.1, U31.7
SDA16: J49.3, J50.3, J51.3, R97.1, U33.7
SDA17: J52.3, J53.3, J54.3, R103.1, U35.7
SDA18: J55.3, J56.3, J57.3, R109.1, U37.7
SDA19: J58.3, J59.3, J60.3, R115.1, U39.7
SDA20: J61.3, J62.3, J63.3, R121.1, U41.7
SDA21: J64.3, J65.3, J66.3, R127.1, U43.7
SDA22: J67.3, J68.3, J69.3, R133.1, U45.7
SDA23: J70.3, J71.3, J72.3, R139.1, U47.7
SDA24: J73.3, J74.3, J75.3, R145.1, U49.7
TRIG: Q1.1, TRIG.1, U1.7, U2.2
TRIG1: Q2.1, TRIG1.1, U3.2, U4.7
TRIG2: Q3.1, TRIG2.1, U5.2, U6.7
TRIG3: Q4.1, TRIG3.1, U7.2, U8.7
TRIG4: Q5.1, TRIG4.1, U9.2, U10.7
TRIG5: Q6.1, TRIG5.1, U11.2, U12.7
TRIG6: Q7.1, TRIG6.1, U13.2, U14.7
TRIG7: Q8.1, TRIG7.1, U15.2, U16.7
TRIG8: Q9.1, TRIG8.1, U17.2, U18.7
TRIG9: Q10.1, TRIG9.1, U19.2, U20.7
TRIG10: Q11.1, TRIG10.1, U21.2, U22.7
TRIG11: Q12.1, TRIG11.1, U23.2, U24.7
TRIG12: Q13.1, TRIG12.1, U25.2, U26.7
TRIG13: Q14.1, TRIG13.1, U27.2, U28.7
TRIG14: Q15.1, TRIG14.1, U29.2, U30.7
TRIG15: Q16.1, TRIG15.1, U31.2, U32.7
TRIG16: Q17.1, TRIG16.1, U33.2, U34.7
TRIG17: Q18.1, TRIG17.1, U35.2, U36.7
TRIG18: Q19.1, TRIG18.1, U37.2, U38.7
TRIG19: Q20.1, TRIG19.1, U39.2, U40.7
TRIG20: Q21.1, TRIG20.1, U41.2, U42.7
TRIG21: Q22.1, TRIG21.1, U43.2, U44.7
TRIG22: Q23.1, TRIG22.1, U45.2, U46.7
TRIG23: Q24.1, TRIG23.1, U47.2, U48.7
TRIG24: Q25.1, TRIG24.1, U49.2, U50.7

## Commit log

2021-01-26 Ready for manufacture
2021-02-04 Adding the VM1010 PROD_ID
2021-02-04 Adding SKU
2021-03-10 Adding Example1
2021-03-11 Add Sound_Trigger_Analyzer_1D.py
2021-03-14 2D Analyzer: work in progress
2021-03-15 2D Analyzer works!
2021-03-15 Adding test cases for both analyzers
2021-03-15 Update READMEs
2021-03-16 Checking the markdown theory is correct
2021-03-16 Simplifying the calculation of SY
2021-03-20 Remove New-Parts
2021-04-06 Add product image
